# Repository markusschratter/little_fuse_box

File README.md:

# Power Distribution Boards

This repository contains two power distribution boards: a 12V and a 24V version. Both boards provide multiple protected output channels with automotive fuses and status LEDs.

- Automotive blade fuses (Keystone 3568) for overcurrent protection
- Status LEDs (Kingbright AA4040SURSK) for each output channel
- Molex connectors for reliable power connections
- Multiple input connectors can be mounted for daisy-chaining and connecting with other boards
- Both boards have the same dimensions as Raspberry Pi boards for compatibility with standard mounting solutions

## Specifications

| Board | Input Voltage | Output Channels | Fuse Protection | Max Current/Channel |
|-------|---------------|-----------------|------------------|---------------------|
| 12V | 12V DC | 7 channels | Automotive blade fuse | 5A-30A (fuse dependent) |
| 24V | 24V DC | 4 channels | Automotive blade fuse | 5A-30A (fuse dependent) |

## Overview

### 12V Power Distribution Board
- **7 protected output channels**, each with an automotive blade fuse (Keystone 3568)
- **Input power** via Molex connector
- **Status LEDs** for each output channel

### 24V Power Distribution Board
- **4 protected output channels** with automotive blade fuses
- **Input power** via Molex connectors
- **Status LEDs** for monitoring

## Project Structure

```
little_fuse_box/
├── 12V/                          # 12V power distribution board
│   ├── power_distribution_12V.kicad_sch
│   ├── power_distribution_12V.kicad_pcb
│   ├── power_distribution_12V.kicad_pro
│   └── 3dmodels/                 # 3D models for components
├── 24V/                          # 24V power distribution board
│   ├── power_distribution_24V.kicad_sch
│   ├── power_distribution_24V.kicad_pcb
│   ├── power_distribution_24V.kicad_pro
│   └── 3dmodels/                 # 3D models for components
└── LICENSE
```

## Components

### 12V Board

| Component | Qty | Part Number | Description |
|-----------|-----|-------------|-------------|
| Fuses | 7 | [Keystone 3568](https://www.mouser.at/datasheet/2/215/3568-742601.pdf) | Automotive blade fuse holders |
| LEDs | 8 | [AA4040SURSK](https://www.mouser.com/ProductDetail/Kingbright/AA4040SURSK) | LEDs (Kingbright) |
| Output Connectors | 7 | [39301020](https://www.molex.com/en-us/products/part-detail-pdf/39301020?display=pdf) | Molex Mini-Fit Jr 2-position |
| Power Connector | 1 | [768250004](https://www.molex.com/en-us/products/part-detail-pdf/768250004?display=pdf) | Molex Mega-Fit (J2) |
| Power Connector (DNP) | 1 | [768250004](https://www.molex.com/en-us/products/part-detail-pdf/768250004?display=pdf) | Molex Mega-Fit (J4, optional) |
| Power Connector (DNP) | 1 | [1720650004](https://www.molex.com/en-us/products/part-detail-pdf/1720650004?display=pdf) | Molex (J20, optional) |
| Resistors (5.1kΩ) | 7 | R_0805_2012Metric | (R1-R4, R6-R8) |
| Resistor (500Ω) | 1 | R_0805_2012Metric | (R5) |

**Note**: DNP = Do Not Populate (optional components)

### 24V Board

| Component | Qty | Part Number | Description |
|-----------|-----|-------------|-------------|
| Fuses | 4 | [Keystone 3568](https://www.mouser.at/datasheet/2/215/3568-742601.pdf) | Automotive blade fuse holders |
| LEDs | 6 | [AA4040SURSK](https://www.mouser.com/ProductDetail/Kingbright/AA4040SURSK)| LEDs (Kingbright) |
| Output Connectors | 4 | [39-30-1040](https://www.molex.com/en-us/products/part-detail-pdf/39-30-1040?display=pdf) | Molex Mini-Fit Jr 4-position |
| Power Connectors | 2 | [768250002](https://www.molex.com/en-us/products/part-detail-pdf/768250002?display=pdf) | Molex Mega-Fit 2-position |
| Power Connector | 1 | [172065-0002](https://www.molex.com/en-us/products/part-detail-pdf/172065-0002?display=pdf) | Molex Mega-Fit 2-position |
| Resistors (11kΩ) | 5 | R_0805_2012Metric |  |

**Note**: DNP = Do Not Populate (optional components)

## Design Files

All design files are in KiCad 8.0 format (`.kicad_sch`, `.kicad_pcb`, `.kicad_pro`). 3D STEP and STL models of the boards and components are included in the `3dmodels/` directories.

**3D Board Models:**
- 12V Board: [STEP file](12V/3dmodels/power_distribution_12V.step) | [STL file](12V/3dmodels/power_distribution_12V.stl)
- 24V Board: [STEP file](24V/3dmodels/power_distribution_24V.step) | [STL file](24V/3dmodels/power_distribution_24V.stl)

**Assembly Notes**: Use appropriate automotive blade fuses, verify LED polarity, use proper wire gauge, follow Molex crimping specifications.

## Acknowledgments

Thanks to **Matteo Valentini** for review and modifications.

## License

Licensed under the Apache License, Version 2.0. See [LICENSE](LICENSE) file for details.

## Contributing

Contributions are welcome! Please feel free to submit issues or pull requests.

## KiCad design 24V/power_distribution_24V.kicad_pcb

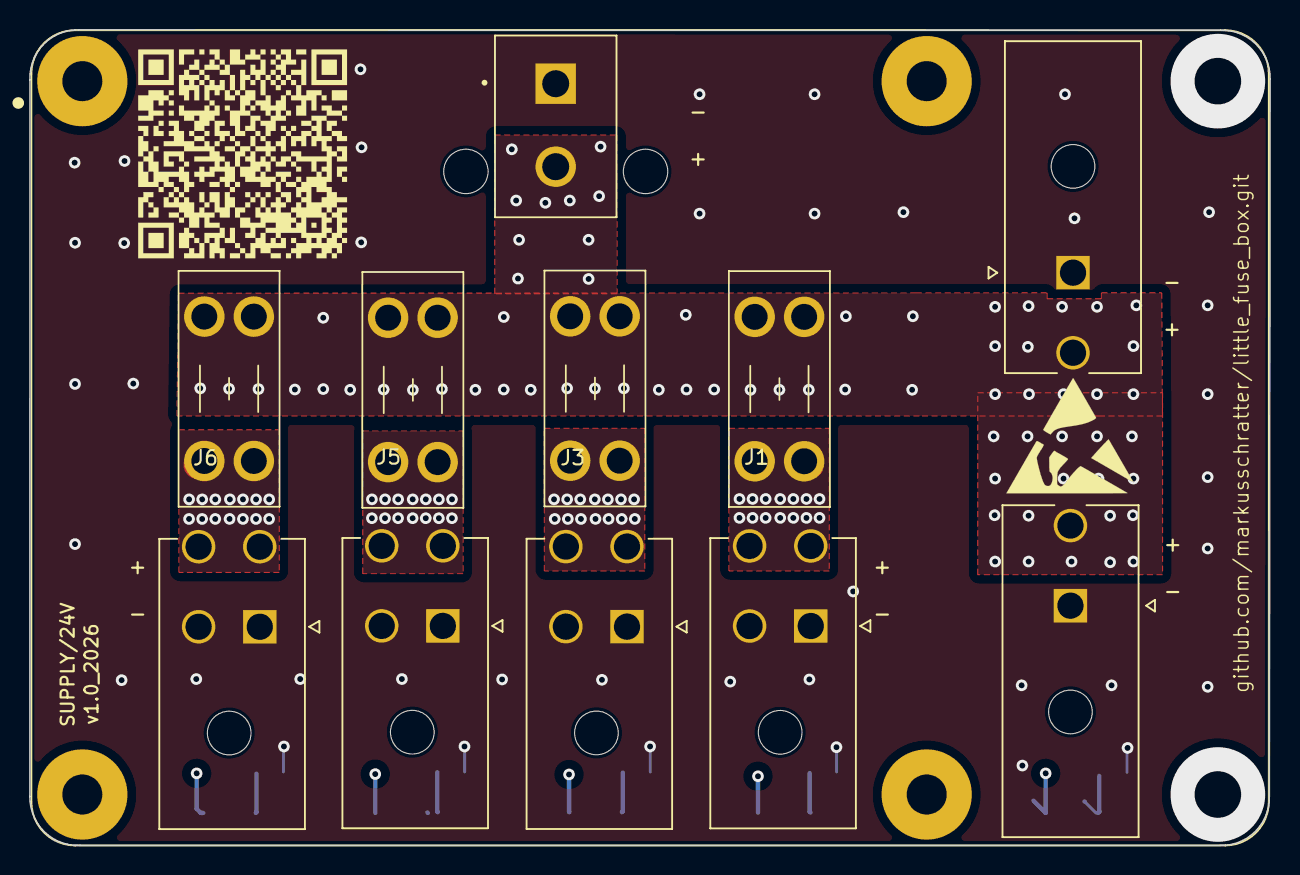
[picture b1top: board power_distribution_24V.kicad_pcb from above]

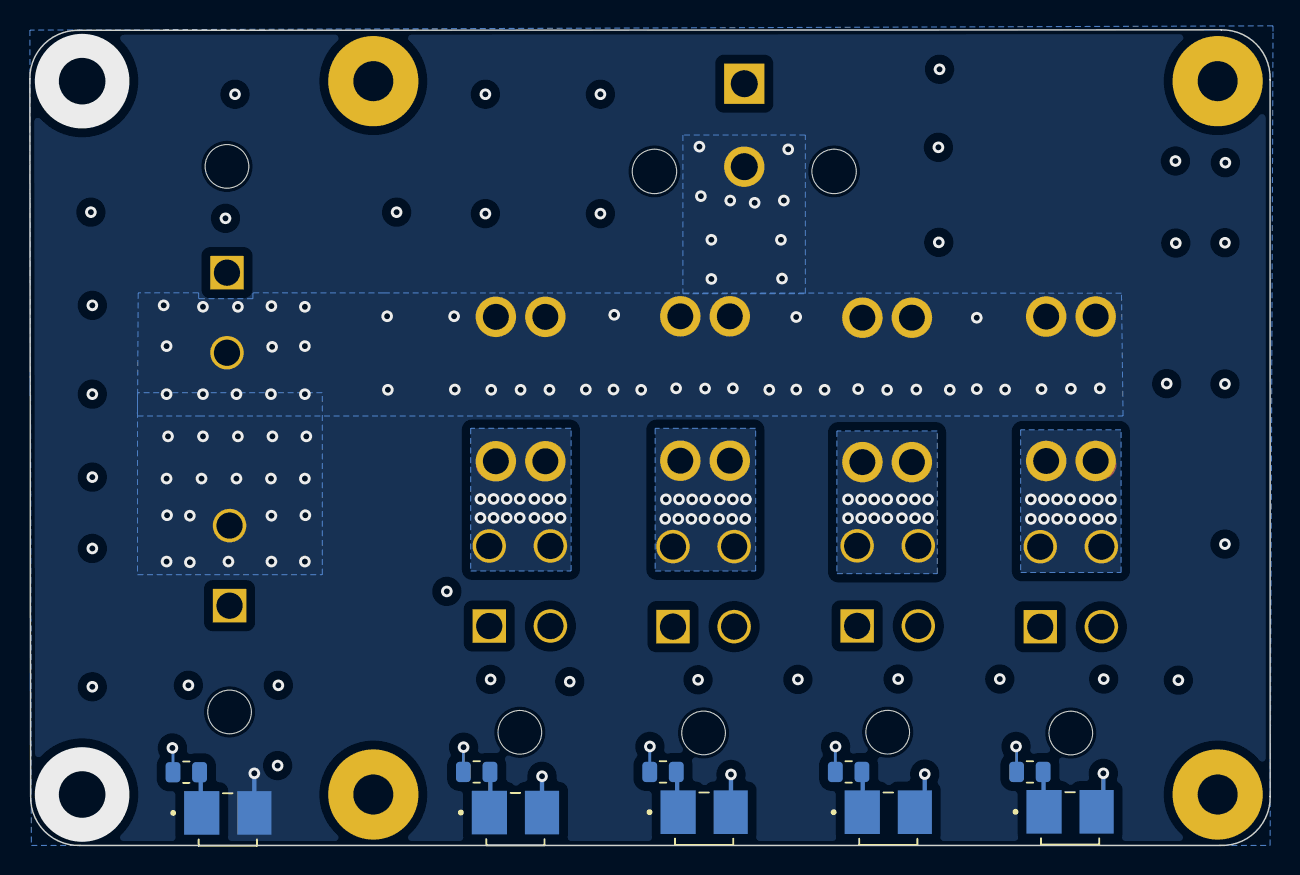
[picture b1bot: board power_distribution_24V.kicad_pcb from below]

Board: 4 copper layers, 85.2 x 56.0 mm, 22 parts (10 on the bottom side), 11 nets.

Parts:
D1, D3, D5, D7, D8: LS_A67K-J1L2-1-0-2-R33-Z; LED_LS_A67K-J1L2-1-0-2-R33-Z
F1, F2, F4, F7: Keystone_3568; Fuseholder_Blade_Mini_Keystone_3568
J1, J3, J5, J6: 39-30-1040; MOLEX_39-30-1040
J2, J8: 768250002; MOLEX_768250002
J4: 172065-0002; MOLEX_172065-0002
R2, R3, R5, R6, R8: 11k; R_0805_2012Metric
U1: RASPBERRY_PCB; MODULE_RASPBERRY_PI_4B_4GB

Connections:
GND: J1.1, J1.2, J2.1, J3.1, J3.2, J4.1, J5.1, J5.2, J6.1, J6.2, J8.1, R2.2, R3.2, R5.2, R6.2, R8.2
unnamed: D1.1, R2.1
unnamed: D1.2, F1.2, J1.3, J1.4
unnamed: D3.1, R3.1
unnamed: D3.2, F2.2, J3.3, J3.4
unnamed: D5.1, R6.1
unnamed: D5.2, F4.2, J5.3, J5.4
unnamed: D7.1, R8.1
unnamed: D7.2, F7.2, J6.3, J6.4
unnamed: D8.1, R5.1
VCC: D8.2, F1.1, F2.1, F4.1, F7.1, J2.2, J4.2, J8.2

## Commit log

2025-11-20 first version of sch/pcb
2025-11-20 corrected resistors for LEDs
2025-12-10 changed layer priorities, increased drill hole sizes
2026-02-21 added 3d models to the pcbs
2026-02-21 added readme
2026-02-22 added 3d model of the board and changeg layer priorities
2026-02-22 added 3d model of the board and changeg layer priorities for 24V version
2026-02-22 minor changes
